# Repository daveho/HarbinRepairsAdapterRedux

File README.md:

# Improved Harbin Repairs Adapter PCBs

This repo has modified versions of the
[Harbin Repairs](https://harbinrepairs.com/) adapter PCBs
for Haswell Optiplex systems (Optiplex 7020, Optiplex 9020,
Optiplex XE2, and Precision T1700.)

These PCBs allow Optiplex motherboards to be used in a standard
Micro-ATX case, which (in my opinion) is a very nice option for
building a useful PC from inexpensive and widely available components
salvaged from decommissioned Dell systems.

I modified the 5/6 pin power switch adapter and the 20 pin front-panel
USB2, audio, and HD LED adapter so that they would not hang off of the
edge of the motherboard. This allows them to be used in cases where
the motherboard is physically close to the edge of the case or
the power supply.

Examples of cases in which the original PCBs don't work:

* Rosewill LINE-M (power switch PCB doesn't fit because the
  power supply obstructs it)
* Compaq Presario SR2000 series (20 pin front-panel PCB doesn't
  fit because the bottom of the case obstructs it)

## Why I created a completely new repository

Originally I forked the Harbin Repairs repository, which is
here: <https://github.com/HarbinRepairs/Dell-Optiplex-MB-Header-Adapters>

However, I was not able to make changes to the KiCad project for
the 20 pin adapter PCB because the filenames are too long.
Also, when I tried to open the PCB design for the 20 pin adapter,
I could not see any traces, but the rats nest also showed that
there were no unconnected nets. I think this might have something
to do with an autorouter being used in the original PCB design.
In any case, I created an entirely new PCB design for this adapter,
based on the original schematic.

## Do they work?

Yes, they do work. I made a video in which I populate and test both
adapters: <https://youtu.be/Dam3fpzKUps>

## Fabrication and construction

I used [OSHPark](https://oshpark.com/) to fabricate the PCBs. It is
incredibly simple: just upload the `kicad_pcb` files, then place your
order.

When you have the PCBs, you will need the following parts:

Part | Needed for | Note
---- | ---------- | ----
[0805 470 Ohm surface-mount resistor](https://www.digikey.com/en/products/detail/te-connectivity-passive-product/CRG0805F470R/2380909) | 20-pin adapter | Exact value is not critical
[2x10 2mm female header](https://www.digikey.com/en/products/detail/sullins-connector-solutions/NPPN102AFCN-RC/804795) | 20-pin adapter | connects to 2x10 male header on motherboard
2x5 2.54mm male header | 20-pin adapter | HD audio: remove second pin in bottom row
2x5 2.54mm male header | 20-pin adapter | USB2: remove first pin in top row
1x2 2.54mm male header | 20-pin adapter | HD LED
[2x3 2mm female header](https://www.digikey.com/en/products/detail/sullins-connector-solutions/NPPN032AFCN-RC/804788) | 5/6-pin adapter | connects to 5 pin header on motherboard
2x3 2.54mm male header | 5/6-pin adapter | power switch, power LED, diagnostic LED

I have linked to 2mm headers and a resistor on Digi-Key that I believe are correct.
However, I bought the 2x10 and 2x3 2mm female headers on Ebay, and I used a resistor
I already had on hand. It likely that any 2mm female headers you find will work.

The 2.54mm pin headers are just standard ones with square pins. You should be able
to find them just about anywhere.

## License

These modified PCBs are licensed under the GPL-3.0 license (the same
as the original PCBs.)

You can send feedback to me at <mailto:david.hovemeyer@gmail.com>.

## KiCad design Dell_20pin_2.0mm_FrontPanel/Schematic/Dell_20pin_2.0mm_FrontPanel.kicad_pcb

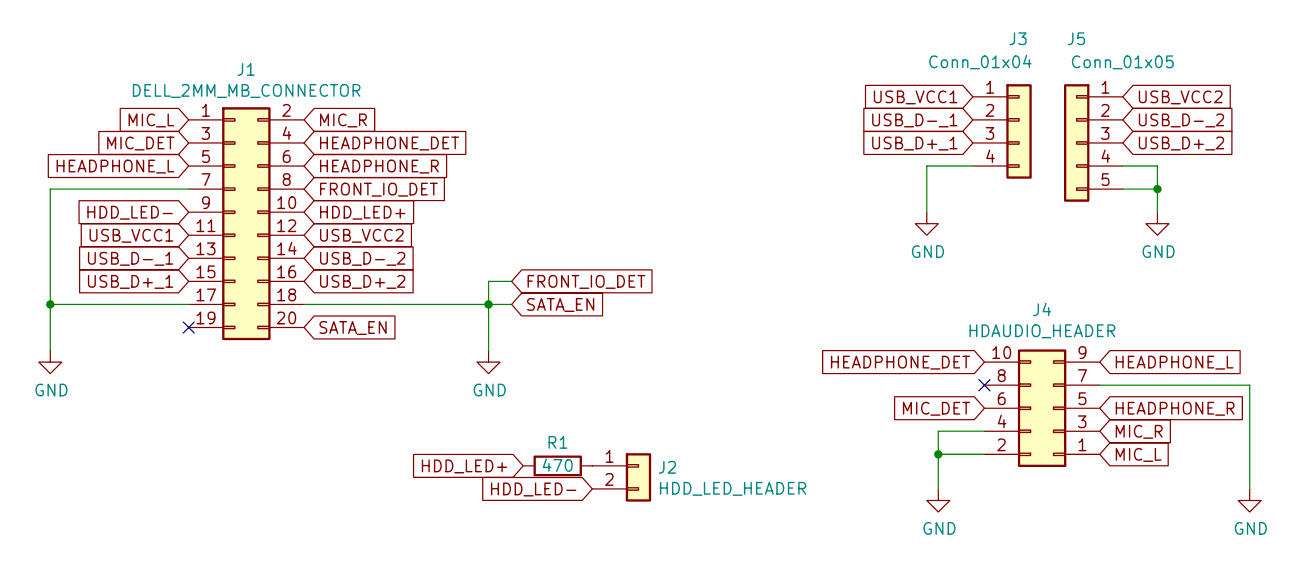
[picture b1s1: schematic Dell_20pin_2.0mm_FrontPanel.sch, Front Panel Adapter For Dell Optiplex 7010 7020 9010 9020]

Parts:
J1: DELL_2MM_MB_CONNECTOR; PinSocket_2x10_P2.00mm_Vertical
J2: HDD_LED_HEADER; PinHeader_1x02_P2.54mm_Vertical
J3: Conn_01x04; PinHeader_1x04_P2.54mm_Vertical
J4: HDAUDIO_HEADER; PinHeader_2x05_P2.54mm_Vertical
J5: Conn_01x05; PinHeader_1x05_P2.54mm_Vertical
R1: 470; R_0805_2012Metric

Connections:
FRONT_IO_DET: J1.7, J1.8, J1.17, J1.18, J1.20, J3.4, J4.2, J4.4, J4.7, J5.4, J5.5
HDD_LED+: J1.10, R1.1
HDD_LED-: J1.9, J2.2
HEADPHONE_DET: J1.4, J4.10
HEADPHONE_L: J1.5, J4.9
HEADPHONE_R: J1.6, J4.5
MIC_DET: J1.3, J4.6
MIC_L: J1.1, J4.1
MIC_R: J1.2, J4.3
unnamed: J2.1, R1.2
USB_D+_1: J1.15, J3.3
USB_D+_2: J1.16, J5.3
USB_D-_1: J1.13, J3.2
USB_D-_2: J1.14, J5.2
USB_VCC1: J1.11, J3.1
USB_VCC2: J1.12, J5.1

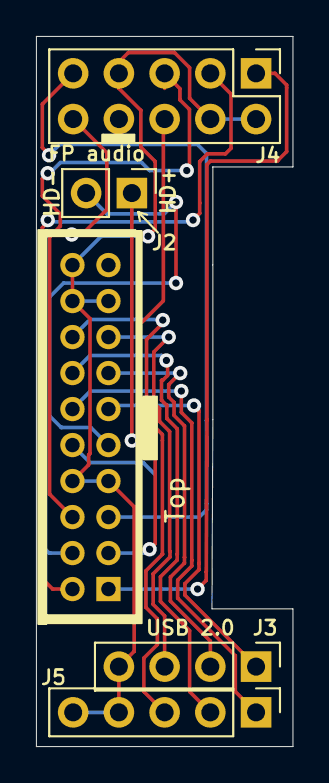
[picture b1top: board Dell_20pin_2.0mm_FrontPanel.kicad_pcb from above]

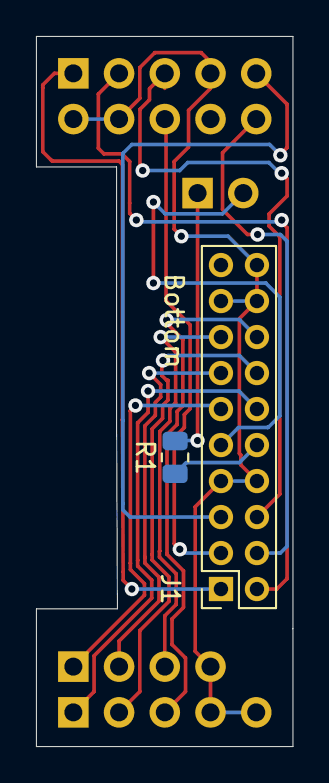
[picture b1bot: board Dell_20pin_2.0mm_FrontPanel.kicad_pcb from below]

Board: 2 copper layers, 14.2 x 39.4 mm, 6 parts (2 on the bottom side), 16 nets.

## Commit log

2022-02-08 create new repo and projects
    The original Harbin Repairs repo has some issues that
    make it difficult to work with: very long filenames,
    spaces in filenames, etc.
    This repo contains my modified versions of the adapter
    PCBs, but with changes to make the files easier to work
    with, and to make the projects more self-contained.
2022-02-08 started a README.md
2022-02-08 move README.md to the correct place
2022-02-08 import original 20pin PCB project
2022-02-08 start new PCB design
    For some reason, when I load the original one in
    pcbnew, it does not show any tracks, but also does
    any rats nest connections.
2022-02-08 placed components
    Note that I still need to make a cutout to avoid
    obstructing the connector for the temperature sensor.
2022-02-08 added cutout for temp sensor connector
    also, set up design rules for OSHPark, and start
    routing
2022-02-08 all traces routed?
2022-04-26 move front-panel USB2 connector
    In the previous version, the part of the PCB where the
    USB2 connector was located bumped up against a capacitor
    on the motherboard. In the revised version, the
    USB2 connector is moved to the "bottom" of the adapter
    PCB, so the cutout can extended to accommodate the
    capacitor.
2022-04-26 redesigned to move the connectors further apart
    In the previous version, the pins of the 2x3 2.54mm
    connector bumped up against the shroud of the 2x3 2mm
    connector on the motherboard. (Not so much that the
    adapter didn't work, but still not ideal.)
    The revised version reorients the 2x3 2.54mm header and
    moves it a bit further from the 2mm connector.
2022-04-26 it helps if you actually route the signals, duh :-)
2022-04-26 add previews of v0.2 designs
2022-05-18 indicate top and bottom on silkscreen
2022-05-18 photo of v0.2 adapters
2022-05-18 update README.md for v0.2 release
2022-05-18 fix link to photo
2022-05-18 fix typo
2022-05-18 another phrasing tweak
2022-05-18 link to video
